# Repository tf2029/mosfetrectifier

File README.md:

Bill of materials: https://docs.google.com/spreadsheets/d/1njoKPeC4yGrjrtJ0lx1mu7r6Y6SiypfscHjnr32lElU/edit?usp=sharing

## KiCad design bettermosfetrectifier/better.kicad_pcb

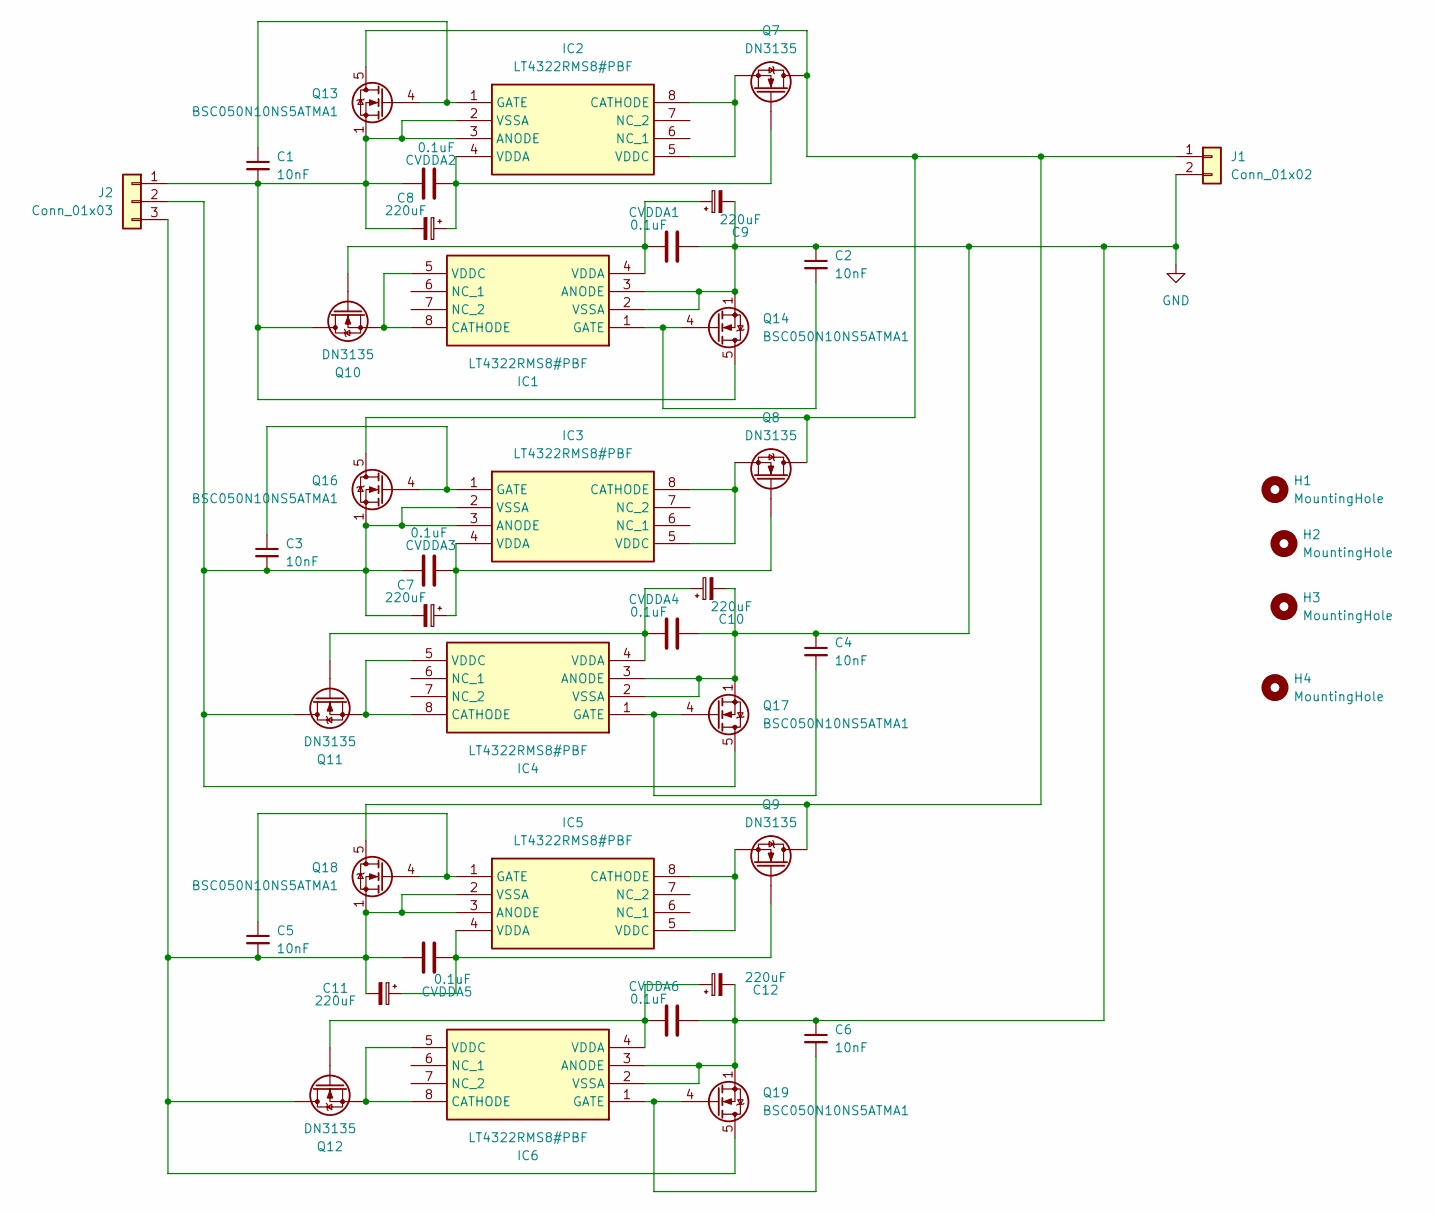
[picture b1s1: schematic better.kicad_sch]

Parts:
C1, C2, C3, C4, C5, C6: 10nF; C_0603_1608Metric
C7, C8, C9, C10, C11, C12: 220uF; CP_Elec_6.3x5.4_Nichicon
CVDDA1, CVDDA2, CVDDA3, CVDDA4, CVDDA5, CVDDA6: 0.1uF; C_0603_1608Metric
H1, H2, H3, H4: MountingHole; MountingHole_3.2mm_M3
IC1, IC2, IC3, IC4, IC5, IC6: LT4322RMS8#PBF; SOP65P490X110-8N; Mouser Part Number 584-LT4322RMS8#PBF
J1: Conn_01x02; TerminalBlock_MaiXu_MX126-5.0-02P_1x02_P5.00mm
J2: Conn_01x03; TerminalBlock_MaiXu_MX126-5.0-03P_1x03_P5.00mm
Q7, Q8, Q9, Q10, Q11, Q12: DN3135; SOT-89-3
Q13, Q14, Q16, Q17, Q18, Q19: BSC050N10NS5ATMA1; TDSON-8-1

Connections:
GND: C2.1, C4.1, C6.1, C9.2, C10.2, C12.2, CVDDA1.1, CVDDA4.1, CVDDA6.1, IC1.2 (VSSA), IC1.3 (ANODE), IC4.2 (VSSA), IC4.3 (ANODE), IC6.2 (VSSA), IC6.3 (ANODE), J1.2, Q14.1 (S), Q14.2 (S), Q14.3 (S), Q17.1 (S), Q17.2 (S), Q17.3 (S), Q19.1 (S), Q19.2 (S), Q19.3 (S)
unnamed: IC1.5 (VDDC), IC1.8 (CATHODE), Q10.3 (S)
unnamed: C2.2, IC1.1 (GATE), Q14.4 (G)
unnamed: C9.1, CVDDA1.2, IC1.4 (VDDA), Q10.1 (G)
unnamed: C1.2, C8.2, CVDDA2.1, IC2.2 (VSSA), IC2.3 (ANODE), J2.1, Q10.2 (D), Q13.1 (S), Q13.2 (S), Q13.3 (S), Q14.5 (D)
unnamed: IC2.5 (VDDC), IC2.8 (CATHODE), Q7.3 (S)
unnamed: C1.1, IC2.1 (GATE), Q13.4 (G)
unnamed: C8.1, CVDDA2.2, IC2.4 (VDDA), Q7.1 (G)
unnamed: C3.2, C7.2, CVDDA3.1, IC3.2 (VSSA), IC3.3 (ANODE), J2.2, Q11.2 (D), Q16.1 (S), Q16.2 (S), Q16.3 (S), Q17.5 (D)
unnamed: IC3.5 (VDDC), IC3.8 (CATHODE), Q8.3 (S)
unnamed: C3.1, IC3.1 (GATE), Q16.4 (G)
unnamed: C7.1, CVDDA3.2, IC3.4 (VDDA), Q8.1 (G)
unnamed: IC4.5 (VDDC), IC4.8 (CATHODE), Q11.3 (S)
unnamed: C4.2, IC4.1 (GATE), Q17.4 (G)
unnamed: C10.1, CVDDA4.2, IC4.4 (VDDA), Q11.1 (G)
unnamed: C5.2, C11.2, CVDDA5.1, IC5.2 (VSSA), IC5.3 (ANODE), J2.3, Q12.2 (D), Q18.1 (S), Q18.2 (S), Q18.3 (S), Q19.5 (D)
unnamed: IC5.5 (VDDC), IC5.8 (CATHODE), Q9.3 (S)
unnamed: C5.1, IC5.1 (GATE), Q18.4 (G)
unnamed: C11.1, CVDDA5.2, IC5.4 (VDDA), Q9.1 (G)
unnamed: IC6.5 (VDDC), IC6.8 (CATHODE), Q12.3 (S)
unnamed: C6.2, IC6.1 (GATE), Q19.4 (G)
unnamed: C12.1, CVDDA6.2, IC6.4 (VDDA), Q12.1 (G)
unnamed: J1.1, Q7.2 (D), Q8.2 (D), Q9.2 (D), Q13.5 (D), Q16.5 (D), Q18.5 (D)

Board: 2 copper layers, 42 parts (0 on the bottom side), 23 nets, no tracks yet.
